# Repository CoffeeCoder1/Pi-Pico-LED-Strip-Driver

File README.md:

# Pi Pico LED Strip Driver

An LED strip driver based around a Pi Pico.

This is a pretty simple project, just a bare-minimum PCB for getting an analog RGB strip driven off a Pi Pico's PWM outputs.

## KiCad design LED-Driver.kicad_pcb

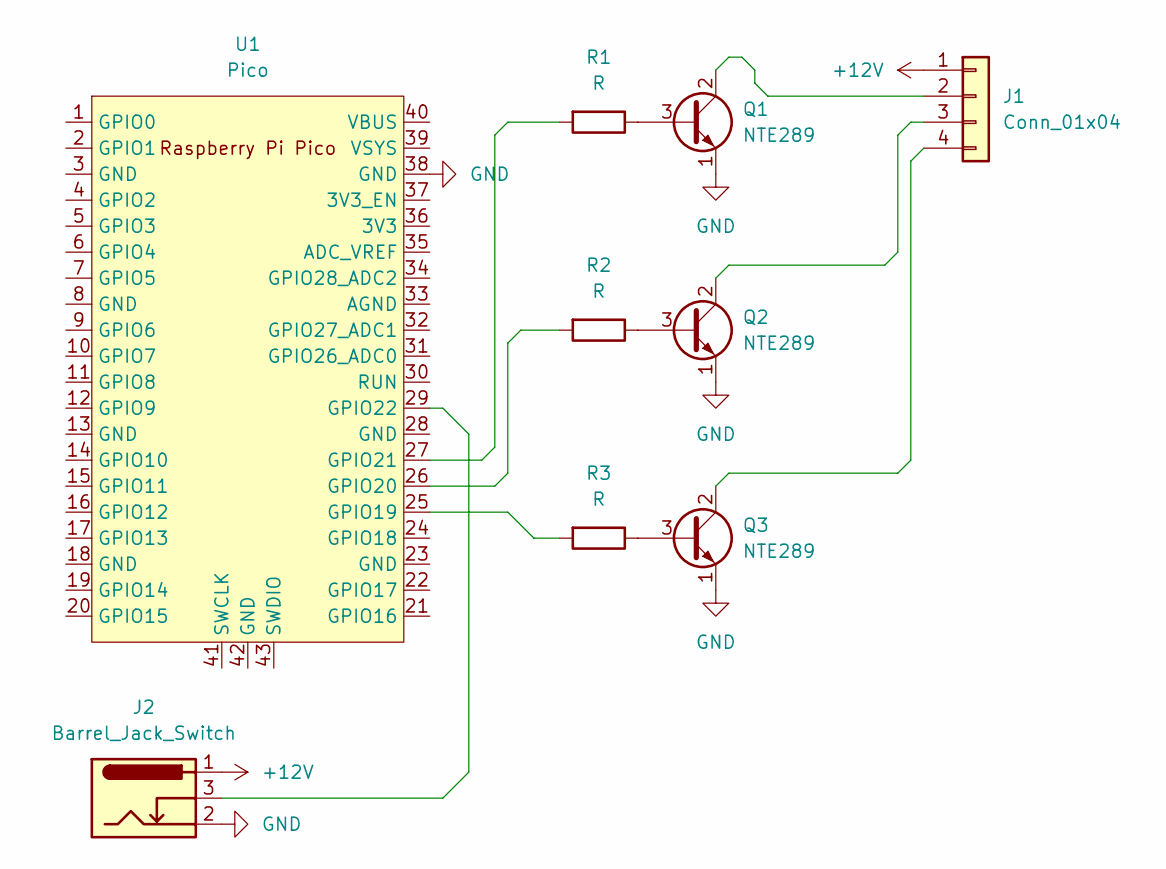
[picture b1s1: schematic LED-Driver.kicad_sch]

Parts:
J1: Conn_01x04; PinHeader_1x04_P2.54mm_Horizontal
J2: Barrel_Jack_Switch; BarrelJack_CUI_PJ-102AH_Horizontal
Q1, Q2, Q3: NTE289; TO-92_Inline
R1, R2, R3: R; R_Axial_DIN0207_L6.3mm_D2.5mm_P10.16mm_Horizontal
U1: Pico; RPi_Pico_SMD_TH

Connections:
+12V: J1.1, J2.1
GND: J2.2, Q1.1 (E), Q2.1 (E), Q3.1 (E), U1.38 (GND)
unnamed: J1.2, Q1.2 (C)
unnamed: J1.3, Q2.2 (C)
unnamed: J1.4, Q3.2 (C)
unnamed: Q1.3 (B), R1.1
unnamed: Q2.3 (B), R2.1
unnamed: Q3.3 (B), R3.1
unnamed: R3.2, U1.25 (GPIO19)
unnamed: R2.2, U1.26 (GPIO20)
unnamed: R1.2, U1.27 (GPIO21)
unnamed: J2.3, U1.29 (GPIO22)

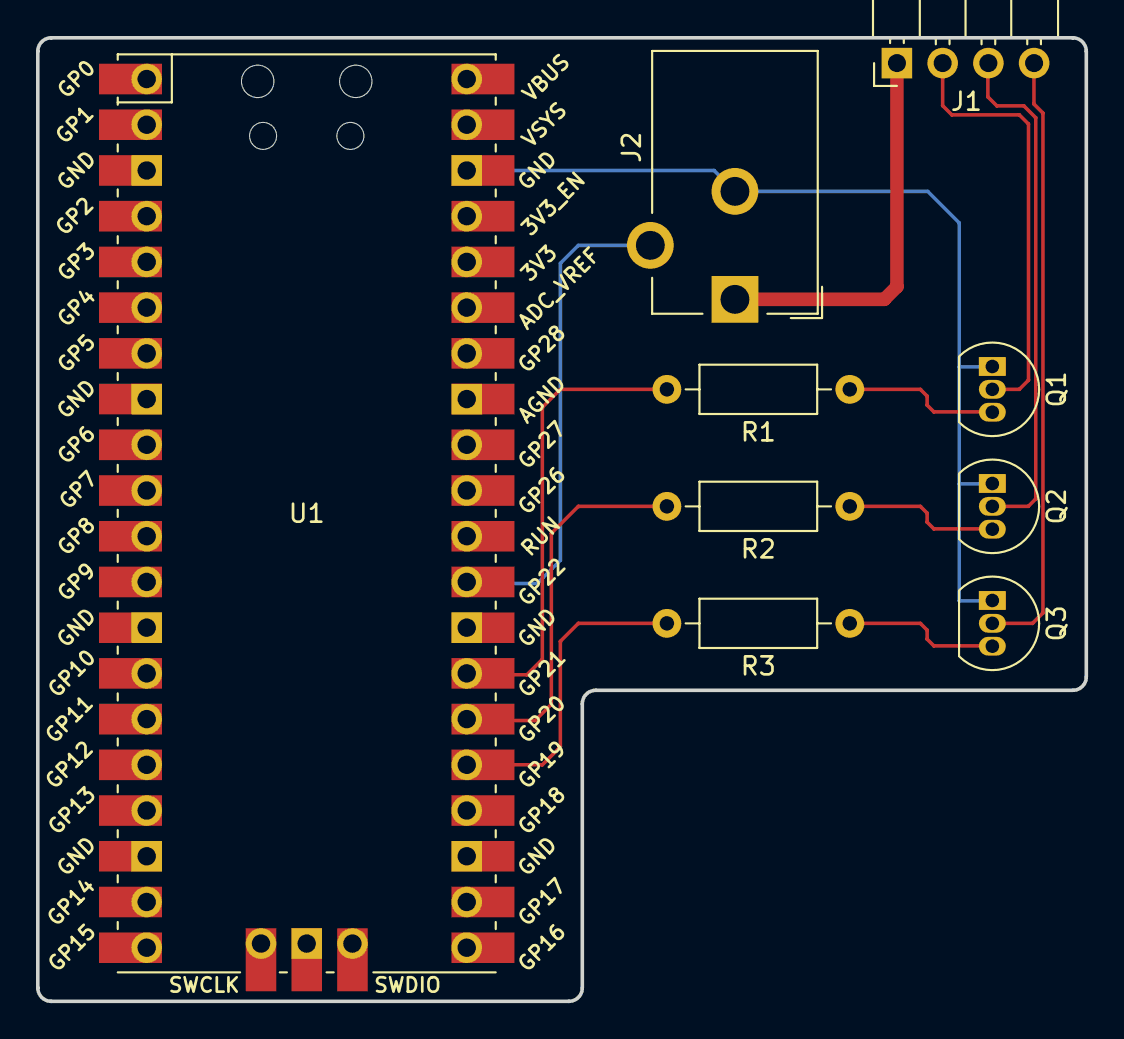
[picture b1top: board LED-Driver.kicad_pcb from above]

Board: 2 copper layers, 58.2 x 53.5 mm, 9 parts (0 on the bottom side), 12 nets.

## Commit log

2024-12-30 Add an initial PCB and swap out the barrel jack
2024-12-31 Add borders to the PCB
2024-12-31 Adjust trace spacing
2024-12-31 Change edge clearance
2024-12-31 Move a silkscreen marking onto the board
2024-12-31 Connect grounds
2024-12-31 Fix the path to the Pi Pico 3D model
2025-01-31 Add a README
